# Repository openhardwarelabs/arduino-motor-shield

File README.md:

# arduino-motor-shield
Arduino simple motor shield

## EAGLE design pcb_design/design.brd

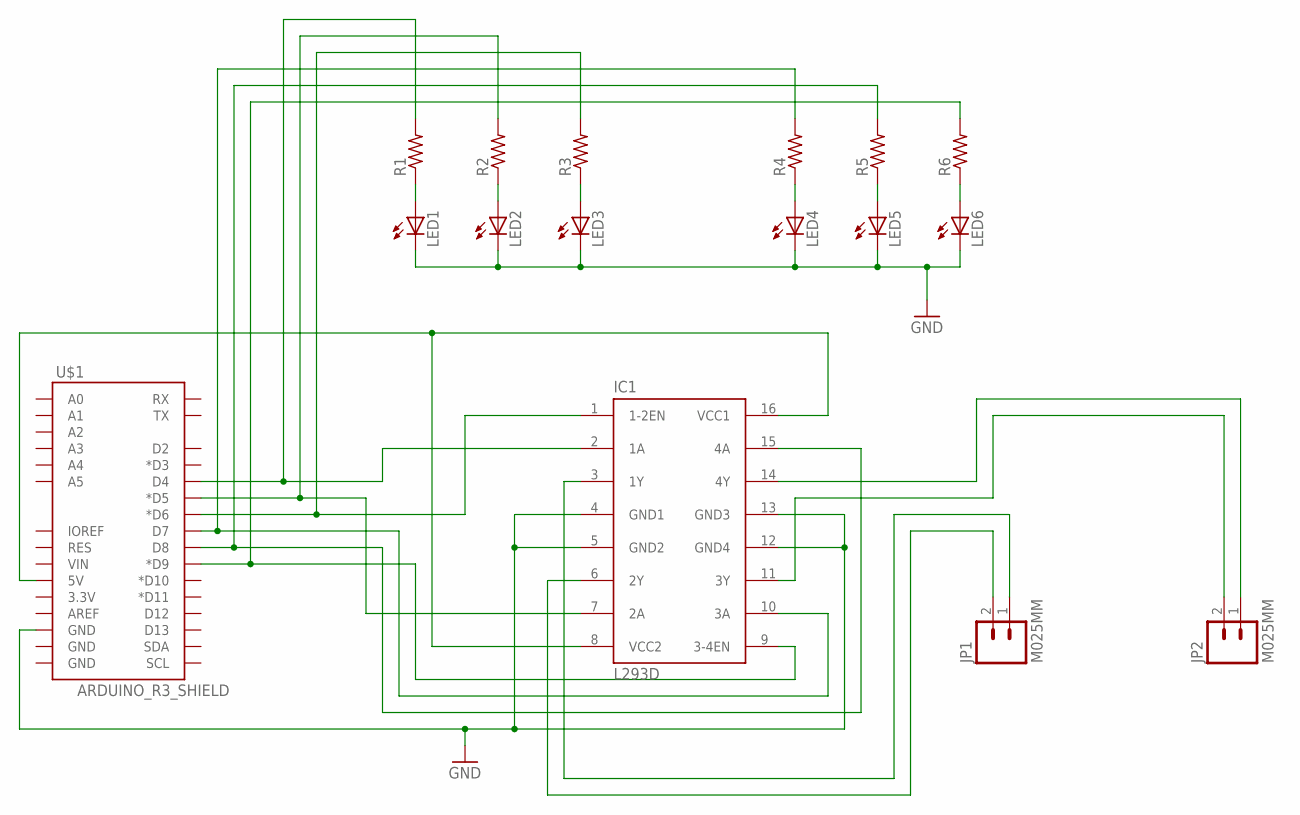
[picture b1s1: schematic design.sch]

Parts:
IC1: L293D; DIL16
JP1, JP2: M025MM; SCREWTERMINAL-5MM-2
LED1, LED2, LED3, LED4, LED5, LED6: LED5MM
R1, R2, R3, R4, R5, R6: R-US_0207/9; 0207/9
U$1: ARDUINO_R3_SHIELD; UNO_R3_SHIELD

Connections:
GND: IC1.4 (GND1), IC1.5 (GND2), IC1.12 (GND4), IC1.13 (GND3), LED1.K (C), LED2.K (C), LED3.K (C), LED4.K (C), LED5.K (C), LED6.K (C), U$1.GND@2 (GND)
unnamed: LED3.A, R3.1
unnamed: LED2.A, R2.1
unnamed: LED1.A, R1.1
unnamed: LED4.A, R4.1
unnamed: LED5.A, R5.1
unnamed: LED6.A, R6.1
unnamed: IC1.11 (3Y), JP2.2
unnamed: IC1.3 (1Y), JP1.1
unnamed: IC1.6 (2Y), JP1.2
unnamed: IC1.8 (VCC2), IC1.16 (VCC1), U$1.5V
unnamed: IC1.14 (4Y), JP2.1
unnamed: IC1.1 (1-2EN), R3.2, U$1.D6 (*D6)
unnamed: IC1.7 (2A), R2.2, U$1.D5 (*D5)
unnamed: IC1.10 (3A), R4.2, U$1.D7
unnamed: IC1.9 (3-4EN), R6.2, U$1.D9 (*D9)
unnamed: IC1.2 (1A), R1.2, U$1.D4
unnamed: IC1.15 (4A), R5.2, U$1.D8

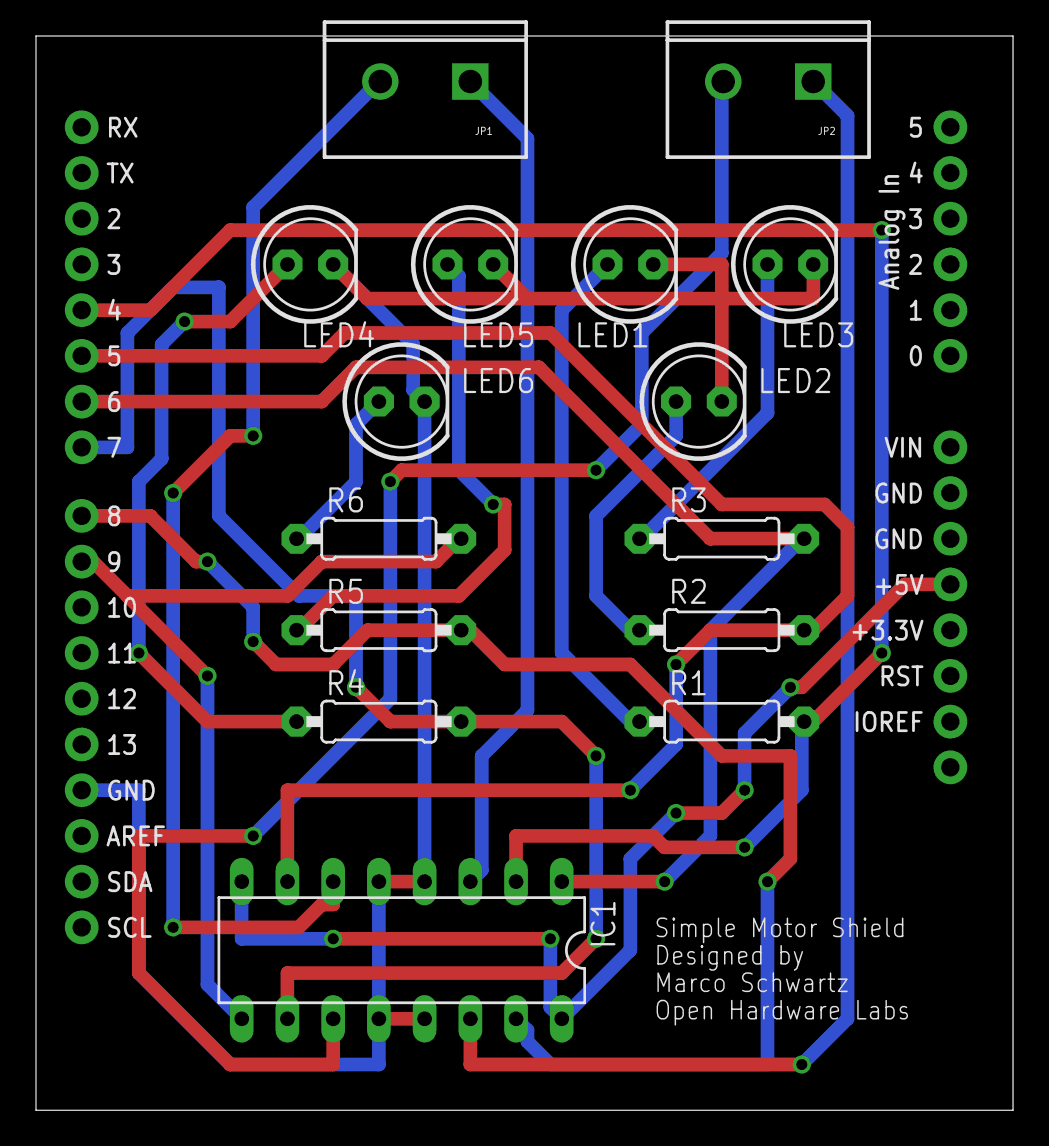
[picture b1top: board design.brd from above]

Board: 2 copper layers, 54.3 x 59.7 mm, 16 parts (0 on the bottom side), 18 nets.

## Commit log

2015-01-19 initial commit with test sketch
2015-01-20 added PCB design

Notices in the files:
parts and their libraries:
SparkFun-Connectors: Licensing: Creative Commons ShareAlike 4.0 International - https://creativecommons.org/licenses/by-sa/4.0
